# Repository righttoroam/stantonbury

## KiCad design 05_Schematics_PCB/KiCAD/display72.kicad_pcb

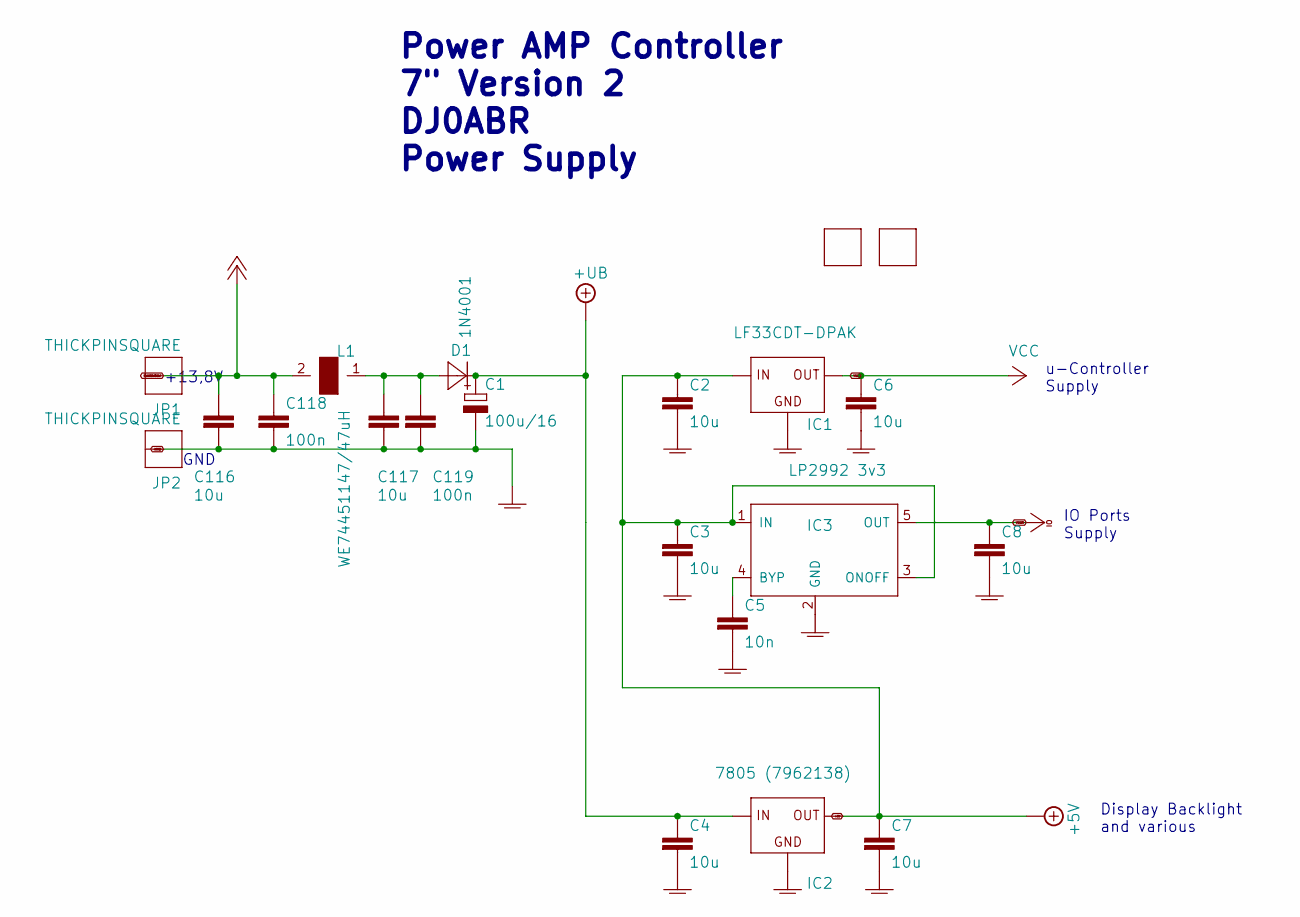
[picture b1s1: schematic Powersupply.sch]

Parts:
C1: 100u/16; E2,5-7
C2, C3, C4, C116, C117: 10u; C0805
C5: 10n; C0603
C6, C7, C8: 10u; C0603
C118, C119: 100n; C0603
D1: 1N4001; MELF
FID1, FID2: FIDUCIAL
IC1: LF33CDT-DPAK; DPACK
IC2: 7805 (7962138); 78SR_SWITCHREG
IC3: LP2992 3v3; SOT23-5
JP1, JP2: THICKPINSQUARE; THICKPIN
L1: WE74451147/47uH; S

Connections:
+5V: C2.1, C3.1, C7.1, IC1.1 (IN), IC2.3 (OUT), IC3.1 (IN), IC3.3 (ONOFF); also elsewhere on the board
+UB: C1.+, C4.1, D1.1 (C), IC2.1 (IN)
unnamed: C5.1, IC3.4 (BYP)
unnamed: C117.1, C119.1, D1.2 (A), L1.1
PLUSZWOELF: C116.1, C118.1, JP1.1, L1.2; also elsewhere on the board
VCC: C6.1, IC1.3 (OUT); also elsewhere on the board

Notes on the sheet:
GND
+13,8V
Power AMP Controller 7" Version 2 DJ0ABR Power Supply
u-Controller Supply
IO Ports Supply
Display Backlight and various

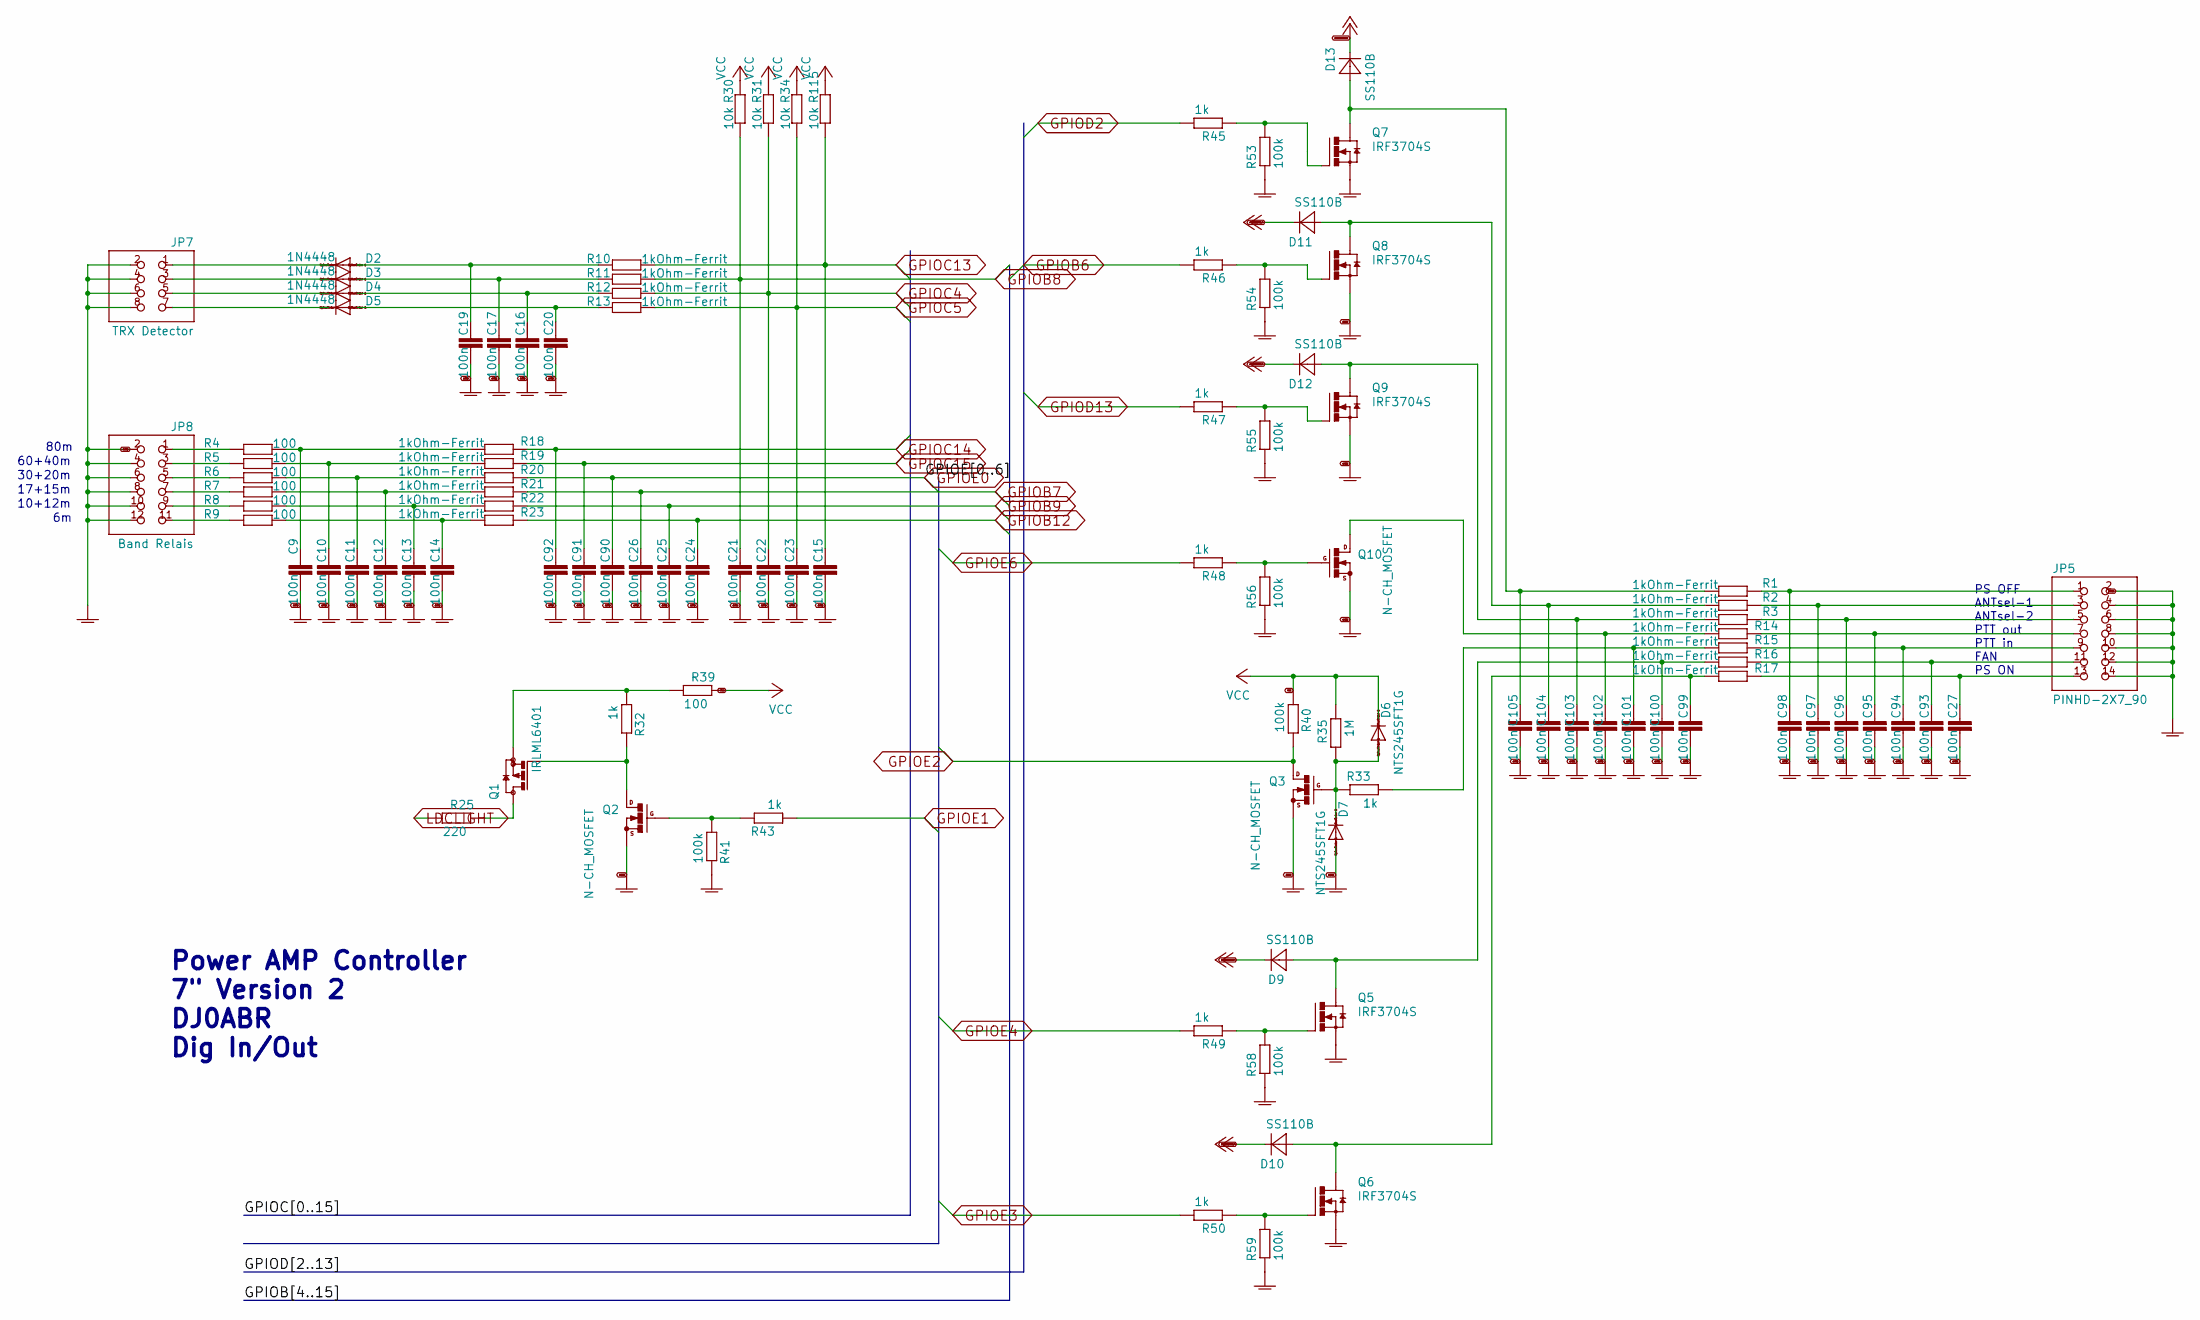
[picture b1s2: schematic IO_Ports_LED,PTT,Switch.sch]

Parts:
C9, C10, C11, C12, C13, C14, C15, C16, C17, C19, C20, C21, C22, C23, C24, C25, C26, C27, C90, C91, C92, C93, C94, C95, C96, C97, C98, C99, C100, C101, C102, C103, C104, C105: 100n; C0603
D2, D3, D4, D5: 1N4448; SOD523
D6, D7: NTS245SFT1G; MINIMELF
D9, D10, D11, D12, D13: SS110B; MELF
JP5: PINHD-2X7_90; 2X07_90
JP7: TRX Detector; 2X04_90
JP8: Band Relais; 2X06_90
Q1: IRLML6401; SOT23
Q2, Q3, Q10: N-CH_MOSFET; SOT23
Q5, Q6, Q7, Q8, Q9: IRF3704S; D2PACK
R1, R2, R3, R10, R11, R12, R13, R14, R15, R16, R17, R18, R19, R20, R21, R22, R23: 1kOhm-Ferrit; R0603
R4, R5, R6, R7, R8, R9, R39: 100; R0603
R25: 220; R0603
R30, R31, R34, R115: 10k; R0603
R32, R33, R43, R45, R46, R47, R48, R49, R50: 1k; R0603
R35: 1M; R0603
R40, R41, R53, R54, R55, R56, R58, R59: 100k; R0603

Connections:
GPIOB6: R46.1; also elsewhere on the board
GPIOB7: C26.1, R21.1; also elsewhere on the board
GPIOB8: C21.1, R11.2, R30.1; also elsewhere on the board
GPIOB9: C25.1, R22.1; also elsewhere on the board
GPIOB12: C24.1, R23.1; also elsewhere on the board
GPIOC4: C22.1, R12.2, R31.1; also elsewhere on the board
GPIOC5: C23.1, R13.2, R34.1; also elsewhere on the board
GPIOC13: C15.1, R10.2, R115.1; also elsewhere on the board
GPIOC14: C92.1, R18.1; also elsewhere on the board
GPIOC15: C91.1, R19.1; also elsewhere on the board
GPIOD2: R45.1; also elsewhere on the board
GPIOD13: R47.1; also elsewhere on the board
GPIOE0: C90.1, R20.1; also elsewhere on the board
GPIOE1: R43.1; also elsewhere on the board
GPIOE2: Q3.3 (D), R40.1; also elsewhere on the board
GPIOE3: R50.1; also elsewhere on the board
GPIOE4: R49.1; also elsewhere on the board
GPIOE6: R48.1; also elsewhere on the board
LDCLIGHT: R25.1; also elsewhere on the board
unnamed: C9.1, R4.2, R18.2
unnamed: C10.1, R5.2, R19.2
unnamed: C11.1, R6.2, R20.2
unnamed: C12.1, R7.2, R21.2
unnamed: C13.1, R8.2, R22.2
unnamed: C14.1, R9.2, R23.2
unnamed: C16.1, D4.A, R12.1
unnamed: C17.1, D3.A, R11.1
unnamed: C19.1, D2.A, R10.1
unnamed: C20.1, D5.A, R13.1
unnamed: C27.1, JP5.13, R17.1
unnamed: C93.1, JP5.11, R16.1
unnamed: C94.1, JP5.9, R15.1
unnamed: C95.1, JP5.7, R14.1
unnamed: C96.1, JP5.5, R3.1
unnamed: C97.1, JP5.3, R2.1
unnamed: C98.1, JP5.1, R1.1
unnamed: C99.1, D10.2 (A), Q6.2 (D), R17.2
unnamed: C100.1, D9.2 (A), Q5.2 (D), R16.2
unnamed: C101.1, R15.2, R33.1
unnamed: C102.1, Q10.3 (D), R14.2
unnamed: C103.1, D12.2 (A), Q9.2 (D), R3.2
unnamed: C104.1, D11.2 (A), Q8.2 (D), R2.2
unnamed: C105.1, D13.2 (A), Q7.2 (D), R1.2
unnamed: D2.C, JP7.1
unnamed: D3.C, JP7.3
unnamed: D4.C, JP7.5
unnamed: D5.C, JP7.7
unnamed: D6.A, D7.C, Q3.1 (G), R33.2, R35.2
unnamed: JP8.1, R4.1
unnamed: JP8.3, R5.1
unnamed: JP8.5, R6.1
unnamed: JP8.7, R7.1
unnamed: JP8.9, R8.1
unnamed: JP8.11, R9.1
unnamed: Q1.1 (G), Q2.3 (D), R32.2
unnamed: Q1.2 (S), R32.1, R39.1
unnamed: Q1.3 (D), R25.2
unnamed: Q2.1 (G), R41.1, R43.2
unnamed: Q5.1 (G), R49.2, R58.1
unnamed: Q6.1 (G), R50.2, R59.1
unnamed: Q7.1 (G), R45.2, R53.1
unnamed: Q8.1 (G), R46.2, R54.1
unnamed: Q9.1 (G), R47.2, R55.1
unnamed: Q10.1 (G), R48.2, R56.1
PLUSZWOELF: D9.1 (C), D10.1 (C), D11.1 (C), D12.1 (C), D13.1 (C); also elsewhere on the board
VCC: D6.C, R30.2, R31.2, R34.2, R35.1, R39.2, R40.2, R115.2; also elsewhere on the board

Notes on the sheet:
80m
60+40m
30+20m
17+15m
10+12m
Power AMP Controller 7" Version 2 DJ0ABR Dig In/Out
PS OFF ANTsel-1 ANTsel-2 PTT out PTT in FAN PS ON

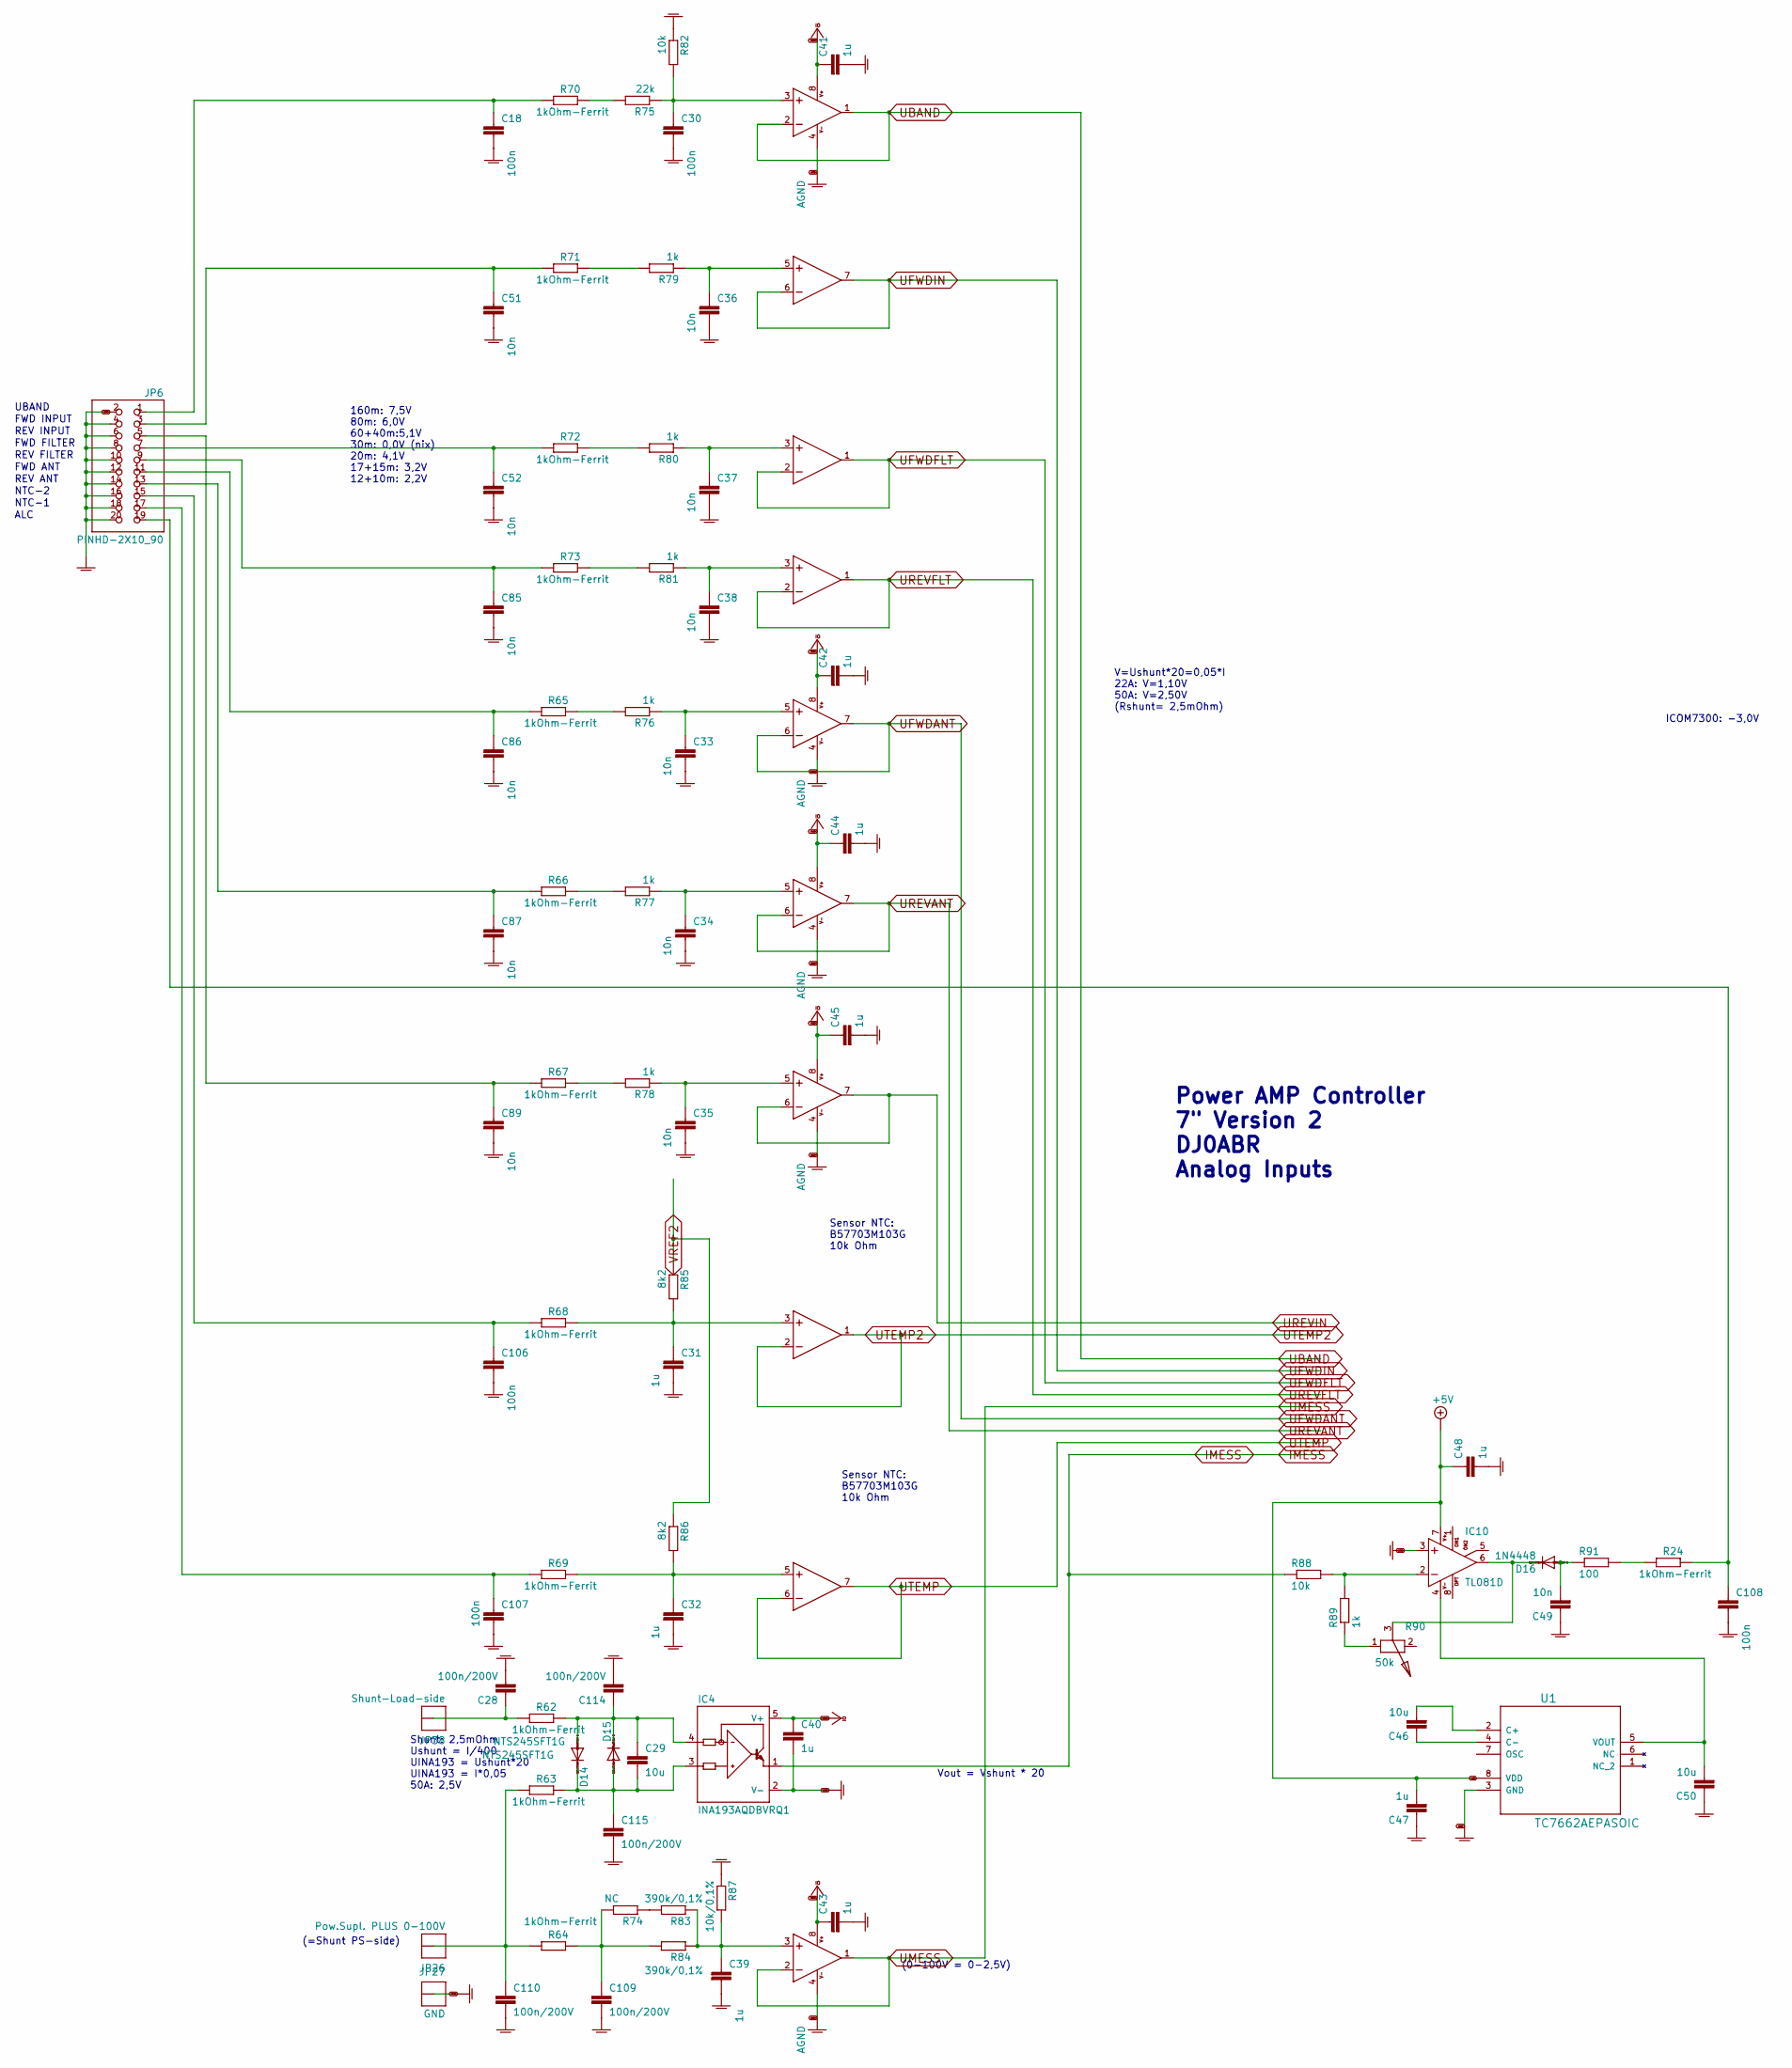
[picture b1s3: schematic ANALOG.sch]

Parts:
C18, C30, C106, C107, C108: 100n; C0603
C28, C109, C110, C114, C115: 100n/200V; C1206K
C29: 10u; C0805
C31, C32, C39, C40, C41, C42, C43, C44, C45, C47, C48: 1u; C0603
C33, C34, C35, C36, C37, C38, C49, C51, C52, C85, C86, C87, C89: 10n; C0603
C46, C50: 10u; C0603
D14, D15: NTS245SFT1G; MINIMELF
D16: 1N4448; SOD523
IC4: INA193AQDBVRQ1; SOT23-5
IC5, IC6, IC7, IC8, IC9: TS27L2C; SO08
IC10: TL081D; SO08
JP6: PINHD-2X10_90; 2X10_90
JP26: Pow.Supl. PLUS 0-100V; THICKPIN
JP27: GND; THICKPIN
JP38: Shunt-Load-side; THICKPIN
R24, R62, R63, R64, R65, R66, R67, R68, R69, R70, R71, R72, R73: 1kOhm-Ferrit; R0603
R74: NC; R0603
R75: 22k; R0603
R76, R77, R78, R79, R80, R81, R89: 1k; R0603
R82, R88: 10k; R0603
R83, R84: 390k/0,1%; R0603
R85, R86: 8k2; R0603
R87: 10k/0,1%; R0603
R90: 50k; MINIPOTI
R91: 100; R0603
U1: TC7662AEPASOIC; SO-8

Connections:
+5V: C47.2, C48.1, IC10.7 (V+), U1.8 (VDD); also elsewhere on the board
IMESS: IC4.1 (OUT), R88.1; also elsewhere on the board
unnamed: C18.1, JP6.1, R70.1
unnamed: C28.1, JP38.1, R62.1
unnamed: C30.1, IC5.3 (+IN), R75.1, R82.2
unnamed: C31.1, IC9.3 (+IN), R68.2, R85.2
unnamed: C32.1, IC8.5 (+IN), R69.2, R86.2
unnamed: C33.1, IC7.5 (+IN), R76.1
unnamed: C34.1, IC9.5 (+IN), R77.1
unnamed: C35.1, IC6.5 (+IN), R78.1
unnamed: C36.1, IC5.5 (+IN), R79.1
unnamed: C37.1, IC6.3 (+IN), R80.1
unnamed: C38.1, IC7.3 (+IN), R81.1
unnamed: C39.1, IC8.3 (+IN), R83.1, R84.1, R87.2
unnamed: C46.1, U1.4 (C-)
unnamed: C46.2, U1.2 (C+)
unnamed: C49.2, D16.A, R91.1
unnamed: C50.2, IC10.4 (V-), U1.5 (VOUT)
unnamed: C51.1, JP6.3, R71.1
unnamed: C52.1, JP6.7, R72.1
unnamed: C85.1, JP6.9, R73.1
unnamed: C86.1, JP6.11, R65.1
unnamed: C87.1, JP6.13, R66.1
unnamed: C89.1, JP6.5, R67.1
unnamed: C106.1, JP6.15, R68.1
unnamed: C107.1, JP6.17, R69.1
unnamed: C108.1, JP6.19, R24.2
unnamed: C109.1, R64.2, R74.2, R84.2
unnamed: C110.1, JP26.1, R63.1, R64.1
unnamed: C29.1, C114.1, D14.A, D15.C, IC4.4 (IN-), R62.2
unnamed: C29.2, C115.1, D14.C, D15.A, IC4.3 (IN+), R63.2
unnamed: D16.C, IC10.6 (OUT), R90.3
unnamed: IC10.2 (-IN), R88.2, R89.2
unnamed: R24.1, R91.2
unnamed: R65.2, R76.2
unnamed: R66.2, R77.2
unnamed: R67.2, R78.2
unnamed: R70.2, R75.2
unnamed: R71.2, R79.2
unnamed: R72.2, R80.2
unnamed: R73.2, R81.2
unnamed: R74.1, R83.2
unnamed: R89.1, R90.1
UBAND: IC5.1 (OUT), IC5.2 (-IN); also elsewhere on the board
UFWDFLT: IC6.1 (OUT), IC6.2 (-IN); also elsewhere on the board
UFWDIN: IC5.6 (-IN), IC5.7 (OUT); also elsewhere on the board
UMESS: IC8.1 (OUT), IC8.2 (-IN); also elsewhere on the board
UREVANT: IC9.6 (-IN), IC9.7 (OUT); also elsewhere on the board
UREVFLT: IC7.1 (OUT), IC7.2 (-IN); also elsewhere on the board
UREVIN: IC6.6 (-IN), IC6.7 (OUT); also elsewhere on the board
UTEMP: IC8.6 (-IN), IC8.7 (OUT); also elsewhere on the board
UTEMP2: IC9.1 (OUT), IC9.2 (-IN); also elsewhere on the board
VREF2: R85.1, R86.1; also elsewhere on the board

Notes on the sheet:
(0-100V = 0-2,5V)
Vout = Vshunt * 20
Sensor NTC: B57703M103G 10k Ohm
V=Ushunt*20=0,05*I 22A: V=1,10V 50A: V=2,50V (Rshunt= 2,5mOhm)
ICOM7300: -3,0V
160m: 7,5V 80m: 6,0V 60+40m:5,1V 30m: 0,0V (nix) 20m: 4,1V 17+15m: 3,2V 12+10m: 2,2V
Shunt: 2,5mOhm Ushunt = I/400 UINA193 = Ushunt*20 UINA193 = I*0,05 50A: 2,5V
Power AMP Controller 7" Version 2 DJ0ABR Analog Inputs
UBAND
FWD INPUT
REV INPUT
FWD FILTER
REV FILTER
FWD ANT
REV ANT
NTC-2
NTC-1
ALC
(=Shunt PS-side)

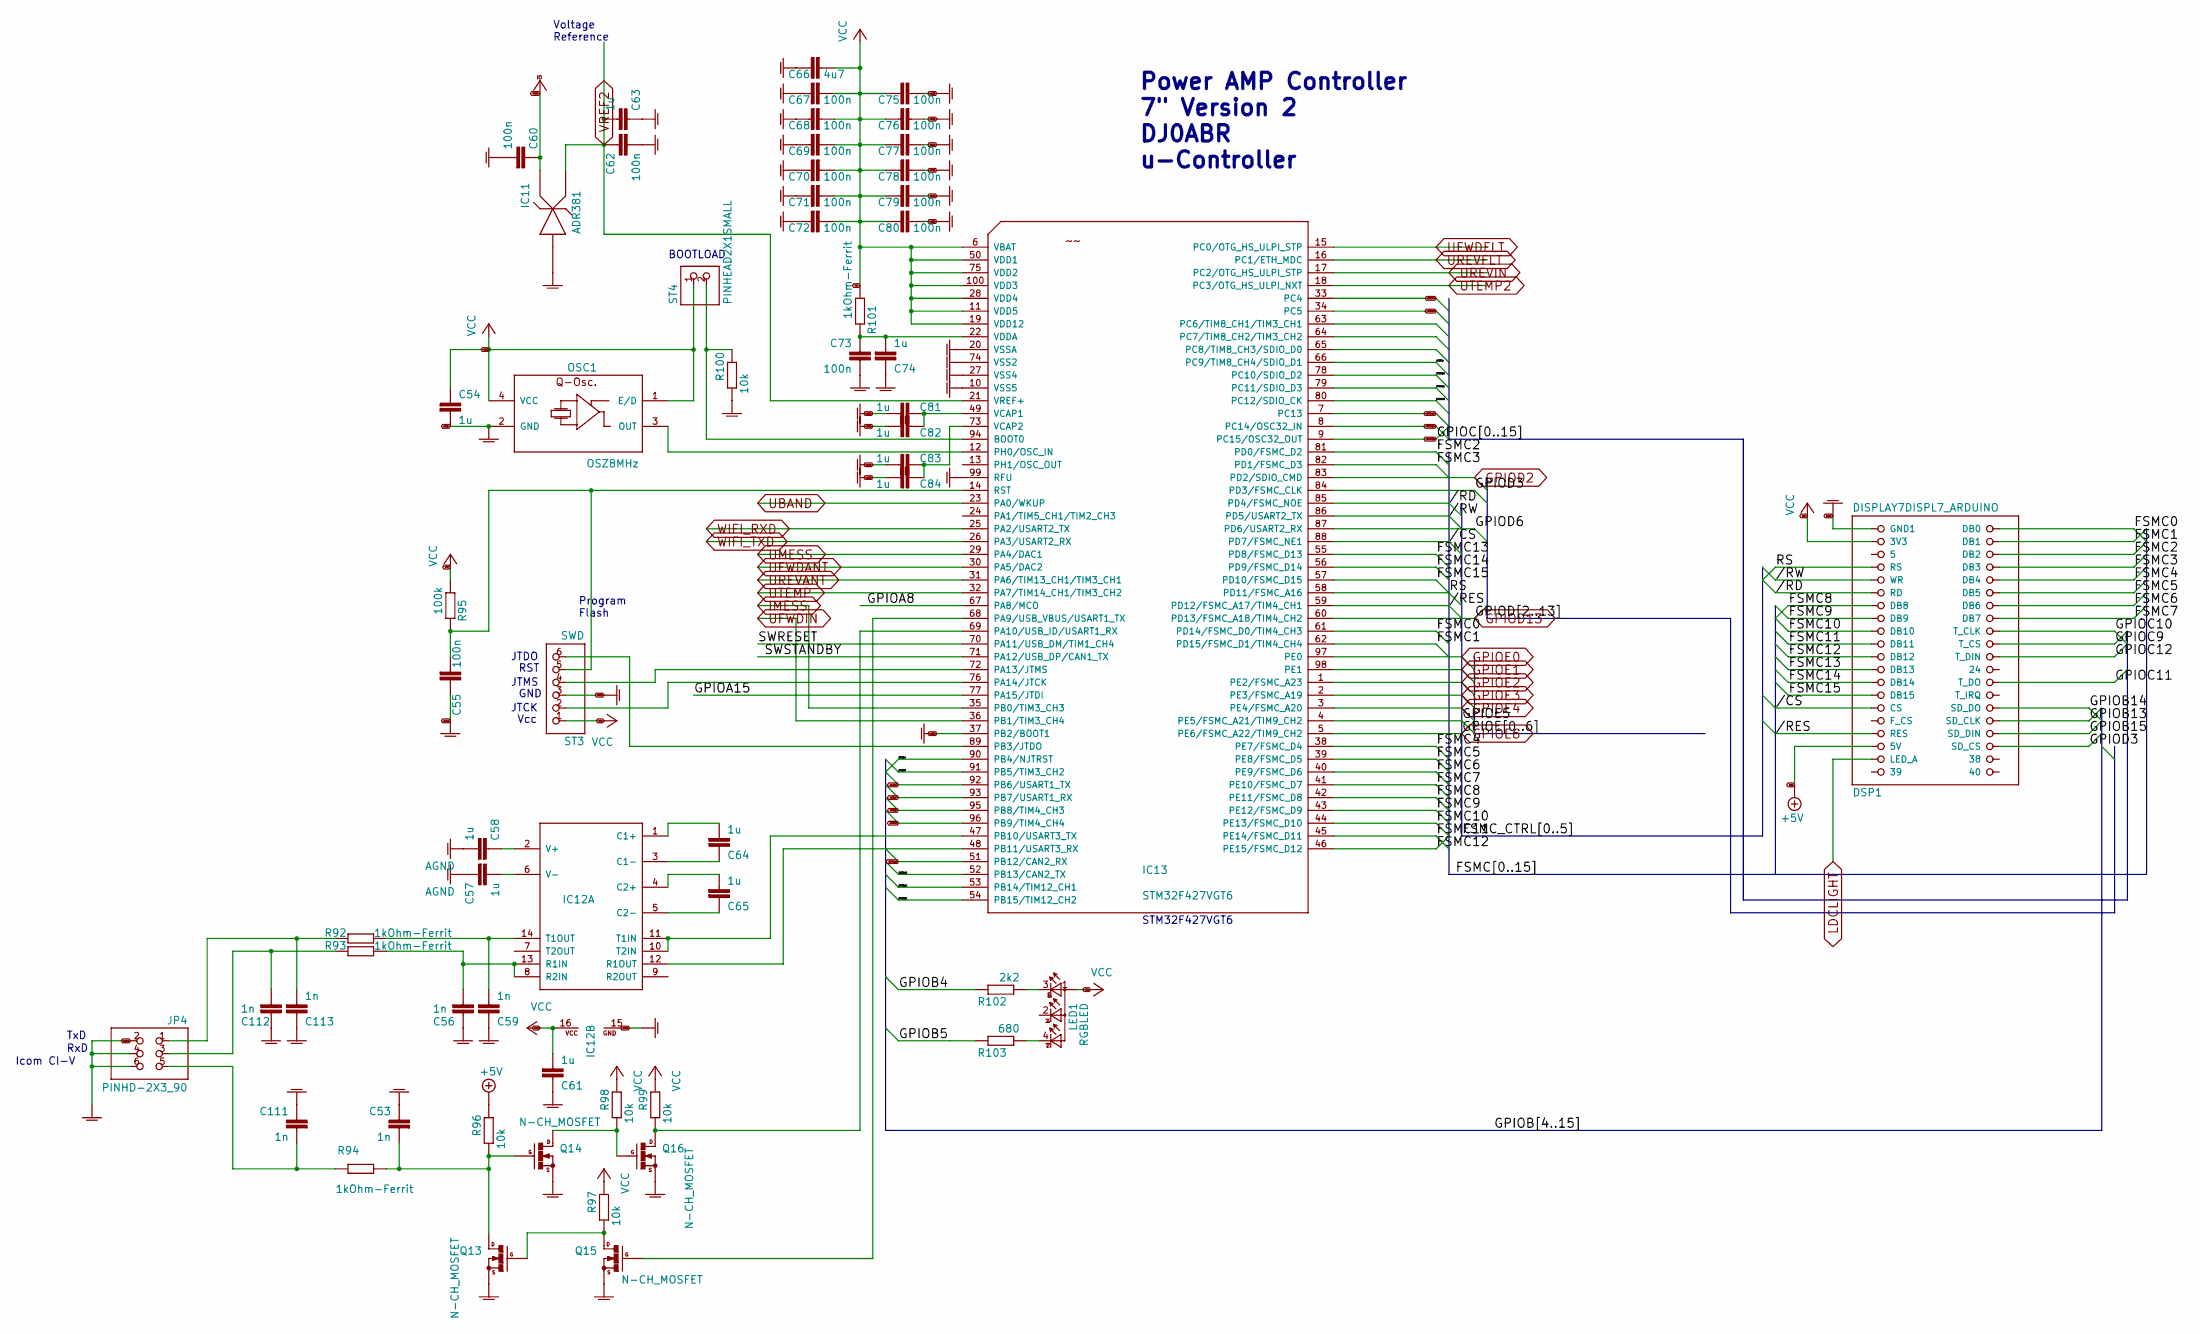
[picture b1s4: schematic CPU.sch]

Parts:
C53, C56, C59, C111, C112, C113: 1n; C0603
C54, C57, C58, C64, C65, C81, C82, C83, C84: 1u; C0603K
C55, C60, C62, C67, C68, C69, C70, C71, C72, C73, C75, C76, C77, C78, C79, C80: 100n; C0603
C61, C63, C74: 1u; C0603
C66: 4u7; C0603
DSP1: DISPLAY7DISPL7_ARDUINO; 2X20
IC11: ADR381; SOT23
IC12: MAX3232; SO16
IC13: STM32F427VGT6; TQFP100
JP4: PINHD-2X3_90; 2X03_90
LED1: RGBLED; PLCC4_WE_LED
OSC1: OSZ8MHz; QOSC_AQO7015
Q13, Q14, Q15, Q16: N-CH_MOSFET; SOT23
R92, R93, R94, R101: 1kOhm-Ferrit; R0603
R95: 100k; R0603
R96, R97, R98, R99, R100: 10k; R0603
R102: 2k2; R0603
R103: 680; R0603
ST3: SWD; PINHEAD6X1
ST4: PINHEAD2X1SMALL; PINHEAD1X2

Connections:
+5V: DSP1.35 (5V), R96.2; also elsewhere on the board
/CPU//CS: DSP1.29 (CS), IC13.88 (PD7/FSMC_NE1)
/CPU//RD: DSP1.11 (RD), IC13.85 (PD4/FSMC_NOE)
/CPU//RES: DSP1.33 (RES), IC13.59 (PD12/FSMC_A17/TIM4_CH1)
/CPU//RW: DSP1.9 (WR), IC13.86 (PD5/USART2_TX)
/CPU/FSMC0: DSP1.2 (DB0), IC13.61 (PD14/FSMC_D0/TIM4_CH3)
/CPU/FSMC1: DSP1.4 (DB1), IC13.62 (PD15/FSMC_D1/TIM4_CH4)
/CPU/FSMC2: DSP1.6 (DB2), IC13.81 (PD0/FSMC_D2)
/CPU/FSMC3: DSP1.8 (DB3), IC13.82 (PD1/FSMC_D3)
/CPU/FSMC4: DSP1.10 (DB4), IC13.38 (PE7/FSMC_D4)
/CPU/FSMC5: DSP1.12 (DB5), IC13.39 (PE8/FSMC_D5)
/CPU/FSMC6: DSP1.14 (DB6), IC13.40 (PE9/FSMC_D6)
/CPU/FSMC7: DSP1.16 (DB7), IC13.41 (PE10/FSMC_D7)
/CPU/FSMC8: DSP1.13 (DB8), IC13.42 (PE11/FSMC_D8)
/CPU/FSMC9: DSP1.15 (DB9), IC13.43 (PE12/FSMC_D9)
/CPU/FSMC10: DSP1.17 (DB10), IC13.44 (PE13/FSMC_D10)
/CPU/FSMC11: DSP1.19 (DB11), IC13.45 (PE14/FSMC_D11)
/CPU/FSMC12: DSP1.21 (DB12), IC13.46 (PE15/FSMC_D12)
/CPU/FSMC13: DSP1.23 (DB13), IC13.55 (PD8/FSMC_D13)
/CPU/FSMC14: DSP1.25 (DB14), IC13.56 (PD9/FSMC_D14)
/CPU/FSMC15: DSP1.27 (DB15), IC13.57 (PD10/FSMC_D15)
/CPU/GPIOA8: IC13.67 (PA8/MCO)
/CPU/GPIOA15: IC13.77 (PA15/JTDI)
/CPU/GPIOB4: IC13.90 (PB4/NJTRST), R102.2
/CPU/GPIOB5: IC13.91 (PB5/TIM3_CH2), R103.2
/CPU/GPIOB13: DSP1.32 (SD_CLK), IC13.52 (PB13/CAN2_TX)
/CPU/GPIOB14: DSP1.30 (SD_DO), IC13.53 (PB14/TIM12_CH1)
/CPU/GPIOB15: DSP1.34 (SD_DIN), IC13.54 (PB15/TIM12_CH2)
/CPU/GPIOC9: DSP1.20 (T_CS), IC13.66 (PC9/TIM8_CH4/SDIO_D1)
/CPU/GPIOC10: DSP1.18 (T_CLK), IC13.78 (PC10/SDIO_D2)
/CPU/GPIOC11: DSP1.26 (T_DO), IC13.79 (PC11/SDIO_D3)
/CPU/GPIOC12: DSP1.22 (T_DIN), IC13.80 (PC12/SDIO_CK)
/CPU/GPIOD3: DSP1.36 (SD_CS), IC13.84 (PD3/FSMC_CLK)
/CPU/GPIOD6: IC13.87 (PD6/USART2_RX)
/CPU/GPIOE5: IC13.4 (PE5/FSMC_A21/TIM9_CH2)
/CPU/RS: DSP1.7 (RS), IC13.58 (PD11/FSMC_A16)
/CPU/SWRESET: IC13.70 (PA11/USB_DM/TIM1_CH4)
/CPU/SWSTANDBY: IC13.71 (PA12/USB_DP/CAN1_TX)
GPIOB6: IC13.92 (PB6/USART1_TX); also elsewhere on the board
GPIOB7: IC13.93 (PB7/USART1_RX); also elsewhere on the board
GPIOB8: IC13.95 (PB8/TIM4_CH3); also elsewhere on the board
GPIOB9: IC13.96 (PB9/TIM4_CH4); also elsewhere on the board
GPIOB12: IC13.51 (PB12/CAN2_RX); also elsewhere on the board
GPIOC4: IC13.33 (PC4); also elsewhere on the board
GPIOC5: IC13.34 (PC5); also elsewhere on the board
GPIOC13: IC13.7 (PC13); also elsewhere on the board
GPIOC14: IC13.8 (PC14/OSC32_IN); also elsewhere on the board
GPIOC15: IC13.9 (PC15/OSC32_OUT); also elsewhere on the board
GPIOD2: IC13.83 (PD2/SDIO_CMD); also elsewhere on the board
GPIOD13: IC13.60 (PD13/FSMC_A18/TIM4_CH2); also elsewhere on the board
GPIOE0: IC13.97 (PE0); also elsewhere on the board
GPIOE1: IC13.98 (PE1); also elsewhere on the board
GPIOE2: IC13.1 (PE2/FSMC_A23); also elsewhere on the board
GPIOE3: IC13.2 (PE3/FSMC_A19); also elsewhere on the board
GPIOE4: IC13.3 (PE4/FSMC_A20); also elsewhere on the board
GPIOE6: IC13.5 (PE6/FSMC_A22/TIM9_CH2); also elsewhere on the board
IMESS: IC13.35 (PB0/TIM3_CH3); also elsewhere on the board
LDCLIGHT: DSP1.37 (LED_A); also elsewhere on the board
unnamed: C53.2, Q13.3 (D), Q14.1 (G), R94.2, R96.1
unnamed: C55.2, IC13.14 (RST), R95.2, ST3.5
unnamed: C56.2, IC12.8 (R2IN), IC12.13 (R1IN), R93.2
unnamed: C57.2, IC12.6 (V-)
unnamed: C58.1, IC12.2 (V+)
unnamed: C59.2, IC12.14 (T1OUT), R92.2
unnamed: C64.1, IC12.3 (C1-)
unnamed: C64.2, IC12.1 (C1+)
unnamed: C65.1, IC12.5 (C2-)
unnamed: C65.2, IC12.4 (C2+)
unnamed: C73.1, C74.2, IC13.22 (VDDA), R101.2
unnamed: C81.2, C82.2, IC13.49 (VCAP1)
unnamed: C83.2, C84.2, IC13.73 (VCAP2)
unnamed: C111.2, JP4.5, R94.1
unnamed: C112.2, JP4.3, R93.1
unnamed: C113.2, JP4.1, R92.1
unnamed: IC12.10 (T2IN), IC12.11 (T1IN), IC13.47 (PB10/USART3_TX)
unnamed: IC12.12 (R1OUT), IC13.48 (PB11/USART3_RX)
unnamed: IC13.12 (PH0/OSC_IN), OSC1.3 (OUT)
unnamed: IC13.68 (PA9/USB_VBUS/USART1_TX), Q15.1 (G)
unnamed: IC13.69 (PA10/USB_ID/USART1_RX), Q16.3 (D), R99.1
unnamed: IC13.72 (PA13/JTMS), ST3.4
unnamed: IC13.76 (PA14/JTCK), ST3.2
unnamed: IC13.89 (PB3/JTDO), ST3.6
unnamed: IC13.94 (BOOT0), R100.2, ST4.2
unnamed: LED1.3 (CRED), R102.1
unnamed: LED1.4 (CGREEN), R103.1
unnamed: Q13.1 (G), Q15.3 (D), R97.1
unnamed: Q14.3 (D), Q16.1 (G), R98.1
UBAND: IC13.23 (PA0/WKUP); also elsewhere on the board
UFWDFLT: IC13.15 (PC0/OTG_HS_ULPI_STP); also elsewhere on the board
UFWDIN: IC13.36 (PB1/TIM3_CH4); also elsewhere on the board
UMESS: IC13.29 (PA4/DAC1); also elsewhere on the board
UREVANT: IC13.31 (PA6/TIM13_CH1/TIM3_CH1); also elsewhere on the board
UREVFLT: IC13.16 (PC1/ETH_MDC); also elsewhere on the board
UREVIN: IC13.17 (PC2/OTG_HS_ULPI_STP); also elsewhere on the board
UTEMP: IC13.32 (PA7/TIM14_CH1/TIM3_CH2); also elsewhere on the board
UTEMP2: IC13.18 (PC3/OTG_HS_ULPI_NXT); also elsewhere on the board
VCC: C54.1, C61.2, C66.2, C67.2, C68.2, C69.2, C70.2, C71.2, C72.2, C75.1, C76.1, C77.1, C78.1, C79.1, C80.1, DSP1.3 (3V3), IC12.16 (VCC), IC13.6 (VBAT), IC13.11 (VDD5), IC13.19 (VDD12), IC13.28 (VDD4), IC13.50 (VDD1), IC13.75 (VDD2), IC13.100 (VDD3), LED1.1 (A2), OSC1.1 (E/D), OSC1.4 (VCC), R95.1, R97.2, R98.2, R99.2, R101.1, ST3.1, ST4.1; also elsewhere on the board
VREF2: C62.1, C63.2, IC11.2 (K1), IC13.21 (VREF+); also elsewhere on the board
WIFI_RXD: IC13.25 (PA2/USART2_TX); also elsewhere on the board
WIFI_TXD: IC13.26 (PA3/USART2_RX); also elsewhere on the board

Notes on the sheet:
BOOTLOAD
Power AMP Controller 7" Version 2 DJ0ABR u-Controller
TxD
RxD
Icom CI-V
Program Flash
Voltage Reference
STM32F427VGT6
JTDO
RST
JTMS
GND
Vcc
JTCK

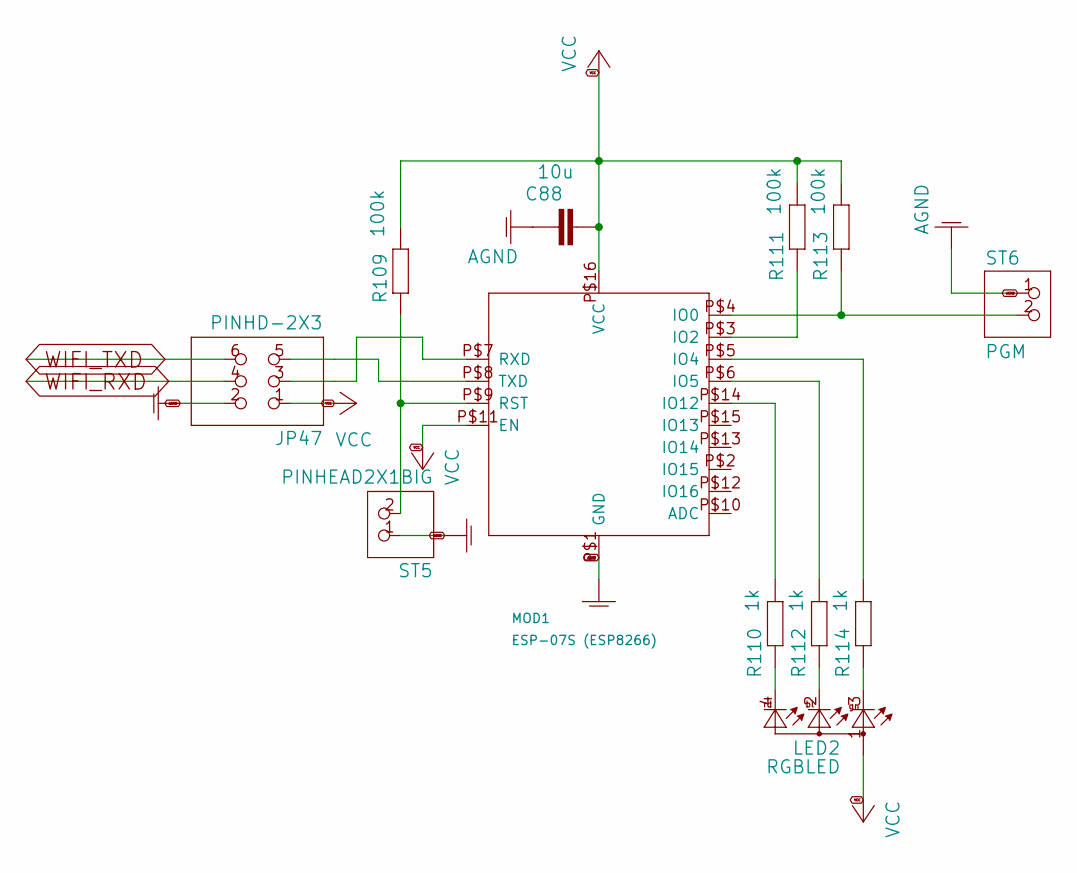
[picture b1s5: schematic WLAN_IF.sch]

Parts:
C88: 10u; C0805K
JP47: PINHD-2X3; 2X03
LED2: RGBLED; PLCC4_WE_LED
MOD1: ESP-07S (ESP8266); ESP8266-12
R109, R111, R113: 100k; R0603
R110, R112, R114: 1k; R0603
ST5: PINHEAD2X1BIG; PINHEAD1X2BIG
ST6: PGM; PINHEAD1X2

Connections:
unnamed: JP47.3, MOD1.P$7 (RXD)
unnamed: JP47.5, MOD1.P$8 (TXD)
unnamed: LED2.2 (CBLUE), R112.1
unnamed: LED2.3 (CRED), R114.1
unnamed: LED2.4 (CGREEN), R110.1
unnamed: MOD1.P$3 (IO2), R111.1
unnamed: MOD1.P$4 (IO0), R113.1, ST6.2
unnamed: MOD1.P$5 (IO4), R114.2
unnamed: MOD1.P$6 (IO5), R112.2
unnamed: MOD1.P$9 (RST), R109.1, ST5.2
unnamed: MOD1.P$14 (IO12), R110.2
VCC: C88.2, JP47.1, LED2.1 (A2), MOD1.P$11 (EN), MOD1.P$16 (VCC), R109.2, R111.2, R113.2; also elsewhere on the board
WIFI_RXD: JP47.4; also elsewhere on the board
WIFI_TXD: JP47.6; also elsewhere on the board

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
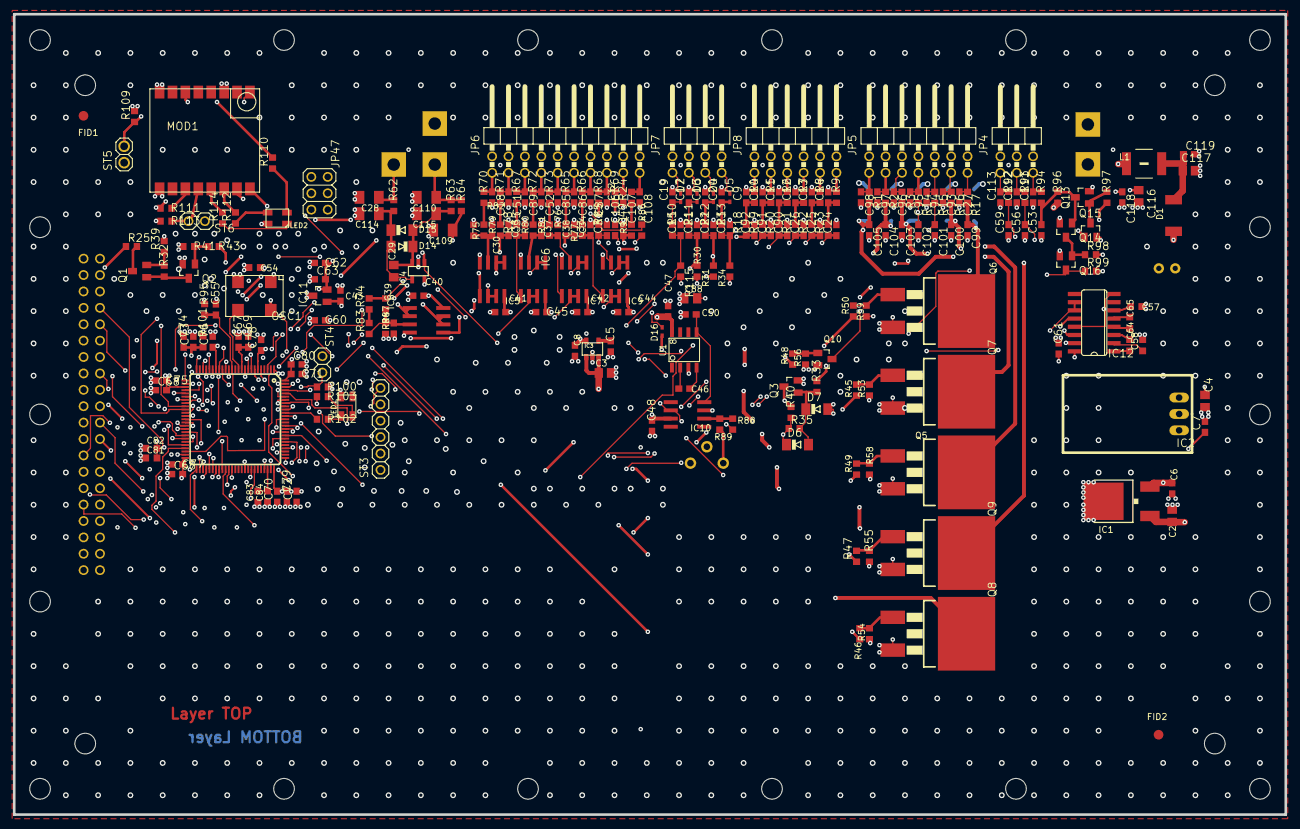
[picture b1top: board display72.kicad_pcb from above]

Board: 4 copper layers, 197.0 x 124.0 mm, 298 parts (0 on the bottom side), 197 nets.

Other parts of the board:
@HOLE0, @HOLE1, @HOLE2, @HOLE3, @HOLE4, @HOLE5, @HOLE6, @HOLE7, @HOLE8, @HOLE9, @HOLE10, @HOLE11, @HOLE12, @HOLE13, @HOLE14, @HOLE15, @HOLE16, @HOLE17: (no value)

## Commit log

2020-11-07 added file structure and heatsink spreadsheet
2020-11-07 test
2020-11-07 added dummy files
2020-11-07 added firmware from DJ0ABR at v1.8
2020-11-08 tidy up, add scehmatics
2020-11-08 updated gitignore
2020-11-09 Updated pin assignments
2020-11-09 Added datasheets, calcs and target spec
2020-11-09 Replaced feasibility spreadsheet with mass est
2020-11-10 More reference materials
2020-11-10 Added ref info on Razvans 600W design
2020-11-11 Controller PCB added
2020-11-28 lastet files added
